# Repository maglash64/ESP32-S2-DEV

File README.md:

# ESP32-S2-DEV
ESP32-S2 Dev Board 
JLCPCB 2313 4-Layer Controlled Impedence Stackup All Components Available on LCSC.  
Features: 
128Mb FLASH. 
USB-C Connector for Programming All Usable GPIOs exposed. 
PCB etched Inverted F Antenna.
Pi Matching required according to choosen PCB stackup.

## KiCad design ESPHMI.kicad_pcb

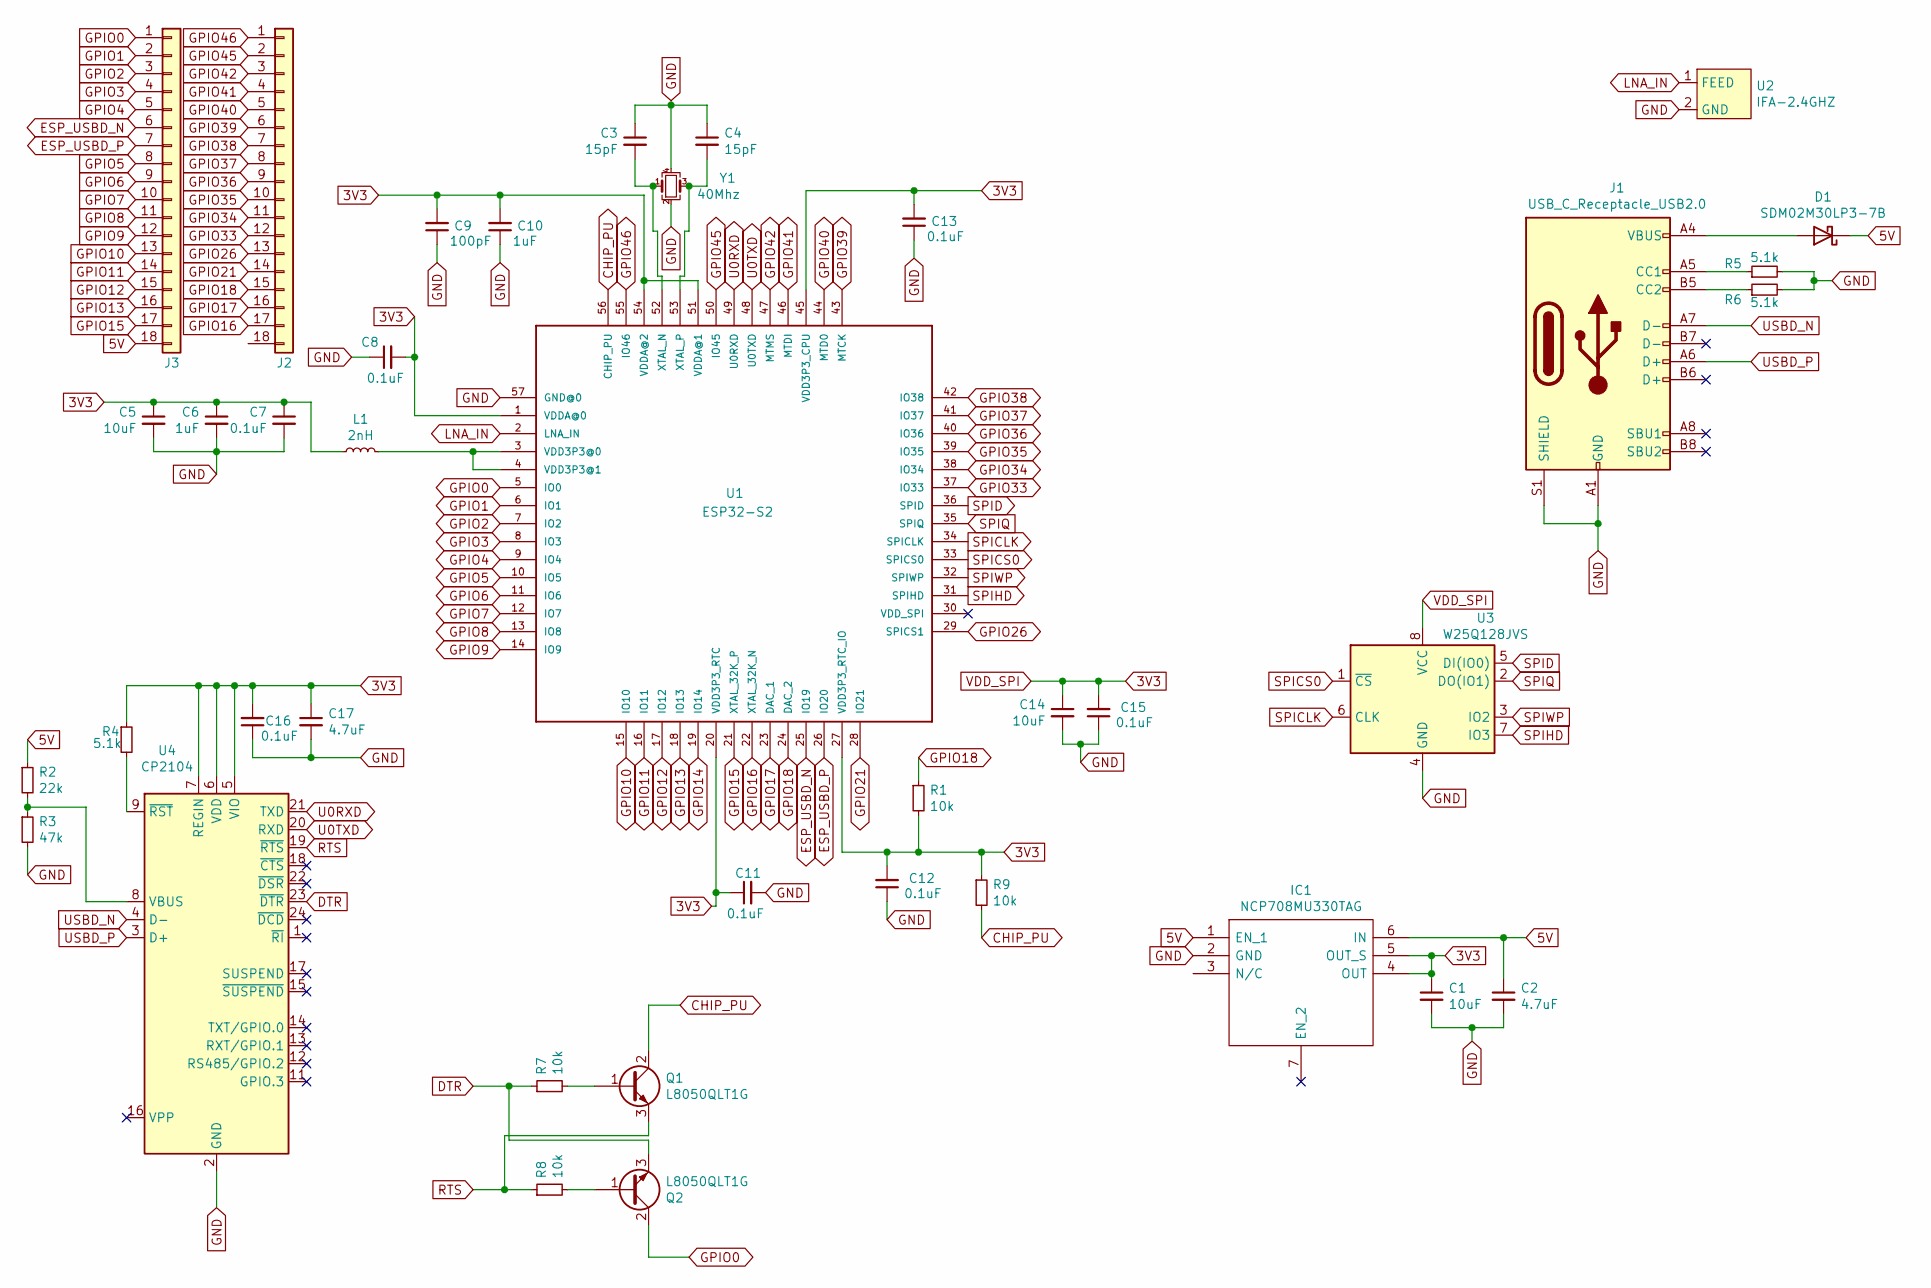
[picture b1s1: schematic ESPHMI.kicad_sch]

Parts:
C1, C5, C14: 10uF; C_01005_0402Metric
C2, C17: 4.7uF; C_01005_0402Metric
C3, C4: 15pF; C_01005_0402Metric
C6, C10: 1uF; C_01005_0402Metric
C7, C8, C11, C12, C13, C15, C16: 0.1uF; C_01005_0402Metric
C9: 100pF; C_01005_0402Metric
D1: SDM02M30LP3-7B; D_0201_0603Metric
IC1: NCP708MU330TAG; SON95P300X300X55-7N; Mouser Part Number 863-NCP708MU330TAG
J1: USB_C_Receptacle_USB2.0; USB_C_Receptacle_HRO_TYPE-C-31-M-12
J2, J3: Conn_01x18; PinHeader_1x18_P2.54mm_Vertical
L1: 2nH; L_01005_0402Metric
Q1, Q2: L8050QLT1G; SOT-23
R1, R7, R8, R9: 10k; R_01005_0402Metric
R2: 22k; R_01005_0402Metric
R3: 47k; R_01005_0402Metric
R4, R5, R6: 5.1k; R_01005_0402Metric
U1: ESP32-S2; QFN40P700X700X90-57T400N
U2: IFA-2.4GHZ
U3: W25Q128JVS; W25Q128JVEIQ
U4: CP2104; QFN-24-1EP_4x4mm_P0.5mm_EP2.6x2.6mm
Y1: 40Mhz; Crystal_SMD_2520-4Pin_2.5x2.0mm

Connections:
3V3: C1.1, C5.1, C6.1, C7.1, C8.2, C9.2, C10.2, C11.1, C12.2, C13.2, C14.1, C15.2, C16.2, C17.1, IC1.4 (OUT), IC1.5 (OUT_S), L1.1, R1.2, R4.1, R9.1, U1.1 (VDDA@0), U1.20 (VDD3P3_RTC), U1.27 (VDD3P3_RTC_IO), U1.45 (VDD3P3_CPU), U1.51 (VDDA@1), U1.54 (VDDA@2), U3.8 (VCC), U4.5 (VIO), U4.6 (VDD), U4.7 (REGIN)
5V: C2.1, D1.1 (K), IC1.1 (EN_1), IC1.6 (IN), J3.18, R2.1
CHIP_PU: Q1.2 (C), R9.2, U1.56 (CHIP_PU)
DTR: Q2.3 (E), R7.1, U4.23 (~DTR)
ESP_USBD_N: J3.6, U1.25 (IO19)
ESP_USBD_P: J3.7, U1.26 (IO20)
GND: C1.2, C2.2, C3.1, C4.1, C5.2, C6.2, C7.2, C8.1, C9.1, C10.1, C11.2, C12.1, C13.1, C14.2, C15.1, C16.1, C17.2, IC1.2 (GND), J1.A1 (GND), J1.A12 (GND), J1.B1 (GND), J1.B12 (GND), J1.S1 (SHIELD), R3.2, R5.2, R6.2, U1.57 (GND@0), U2.2 (GND), U3.4 (GND), U4.2 (GND), U4.25 (GND), Y1.2, Y1.4
GPIO0: J3.1, Q2.2 (C), U1.5 (IO0)
GPIO1: J3.2, U1.6 (IO1)
GPIO2: J3.3, U1.7 (IO2)
GPIO3: J3.4, U1.8 (IO3)
GPIO4: J3.5, U1.9 (IO4)
GPIO5: J3.8, U1.10 (IO5)
GPIO6: J3.9, U1.11 (IO6)
GPIO7: J3.10, U1.12 (IO7)
GPIO8: J3.11, U1.13 (IO8)
GPIO9: J3.12, U1.14 (IO9)
GPIO10: J3.13, U1.15 (IO10)
GPIO11: J3.14, U1.16 (IO11)
GPIO12: J3.15, U1.17 (IO12)
GPIO13: J3.16, U1.18 (IO13)
GPIO14: U1.19 (IO14)
GPIO15: J3.17, U1.21 (XTAL_32K_P)
GPIO16: J2.17, U1.22 (XTAL_32K_N)
GPIO17: J2.16, U1.23 (DAC_1)
GPIO18: J2.15, R1.1, U1.24 (DAC_2)
GPIO21: J2.14, U1.28 (IO21)
GPIO26: J2.13, U1.29 (SPICS1)
GPIO33: J2.12, U1.37 (IO33)
GPIO34: J2.11, U1.38 (IO34)
GPIO35: J2.10, U1.39 (IO35)
GPIO36: J2.9, U1.40 (IO36)
GPIO37: J2.8, U1.41 (IO37)
GPIO38: J2.7, U1.42 (IO38)
GPIO39: J2.6, U1.43 (MTCK)
GPIO40: J2.5, U1.44 (MTD0)
GPIO41: J2.4, U1.46 (MTDI)
GPIO42: J2.3, U1.47 (MTMS)
GPIO45: J2.2, U1.50 (IO45)
GPIO46: J2.1, U1.55 (IO46)
LNA_IN: U1.2 (LNA_IN), U2.1 (FEED)
unnamed: C3.2, U1.52 (XTAL_N), Y1.1
unnamed: C4.2, U1.53 (XTAL_P), Y1.3
unnamed: D1.2 (A), J1.A4 (VBUS), J1.A9 (VBUS), J1.B4 (VBUS), J1.B9 (VBUS)
unnamed: J1.A5 (CC1), R5.1
unnamed: J1.B5 (CC2), R6.1
unnamed: L1.2, U1.3 (VDD3P3@0), U1.4 (VDD3P3@1)
unnamed: Q1.1 (B), R7.2
unnamed: Q2.1 (B), R8.2
unnamed: R2.2, R3.1, U4.8 (VBUS)
unnamed: R4.2, U4.9 (~RST)
RTS: Q1.3 (E), R8.1, U4.19 (~RTS)
SPICLK: U1.34 (SPICLK), U3.6 (CLK)
SPICS0: U1.33 (SPICS0), U3.1 (~CS)
SPID: U1.36 (SPID), U3.5 (DI(IO0))
SPIHD: U1.31 (SPIHD), U3.7 (IO3)
SPIQ: U1.35 (SPIQ), U3.2 (DO(IO1))
SPIWP: U1.32 (SPIWP), U3.3 (IO2)
U0RXD: U1.49 (U0RXD), U4.21 (TXD)
U0TXD: U1.48 (U0TXD), U4.20 (RXD)
USBD_N: J1.A7 (D-), U4.4 (D-)
USBD_P: J1.A6 (D+), U4.3 (D+)

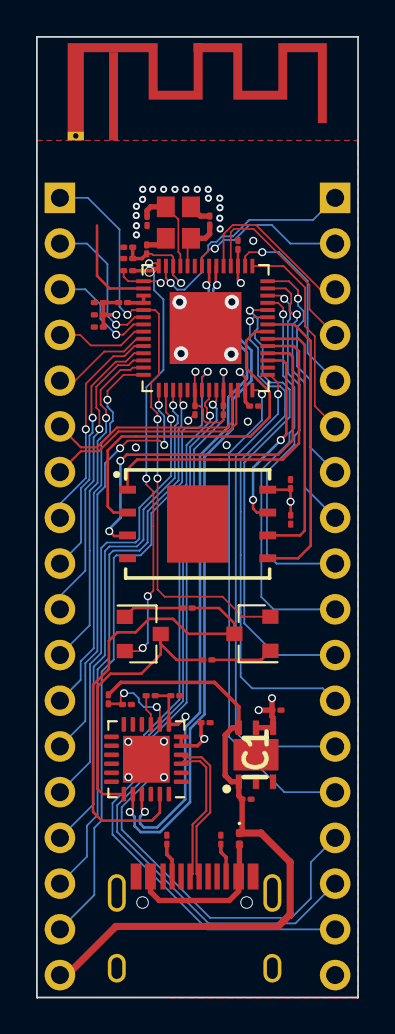
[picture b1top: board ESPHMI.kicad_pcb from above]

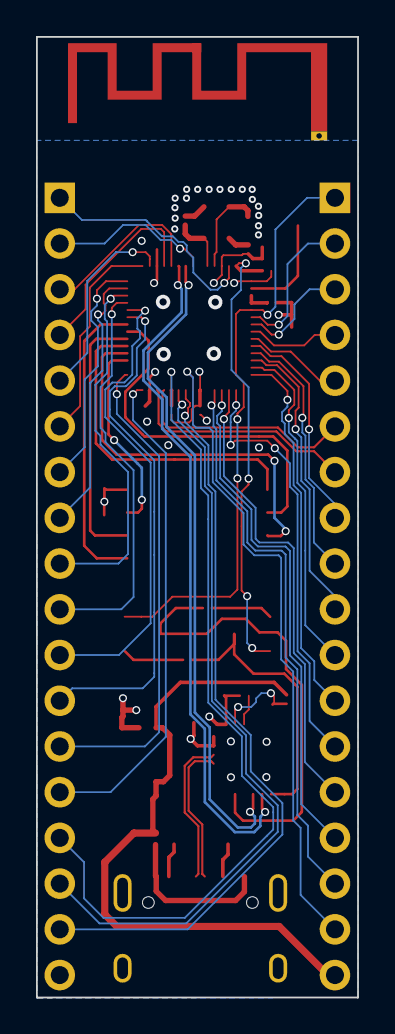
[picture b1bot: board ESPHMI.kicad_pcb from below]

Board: 4 copper layers, 17.8 x 53.4 mm, 39 parts (2 on the bottom side), 61 nets.

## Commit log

2020-12-07 uploaded
2020-12-07 uploaded.
2020-12-07 updated.
2020-12-08 udated.
